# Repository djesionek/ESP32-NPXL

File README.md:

# ESP_NPXL breakout board
This is a breakout board for the ESP-32S (ESP32 chip) and a continuation of the [ESP-NPXL Project](https://github.com/djesionek/ESP-NPXL)

*Work is still in progress*

# Features
Some features that are planned to be added over the old ESP-NPXL project are:

- Integrated FTDI chip and micro USB or USB Type-C connector for easier development
- Integrated LiPo management enabling the chip to charge the battery while connected and seamlessly use its charge after disconnected
- Smaller footprint

# Contributing
Feel free contributing or doing whatever with this design. As board design is only a hobby of mine it's probably 
not a good design anyway ;)

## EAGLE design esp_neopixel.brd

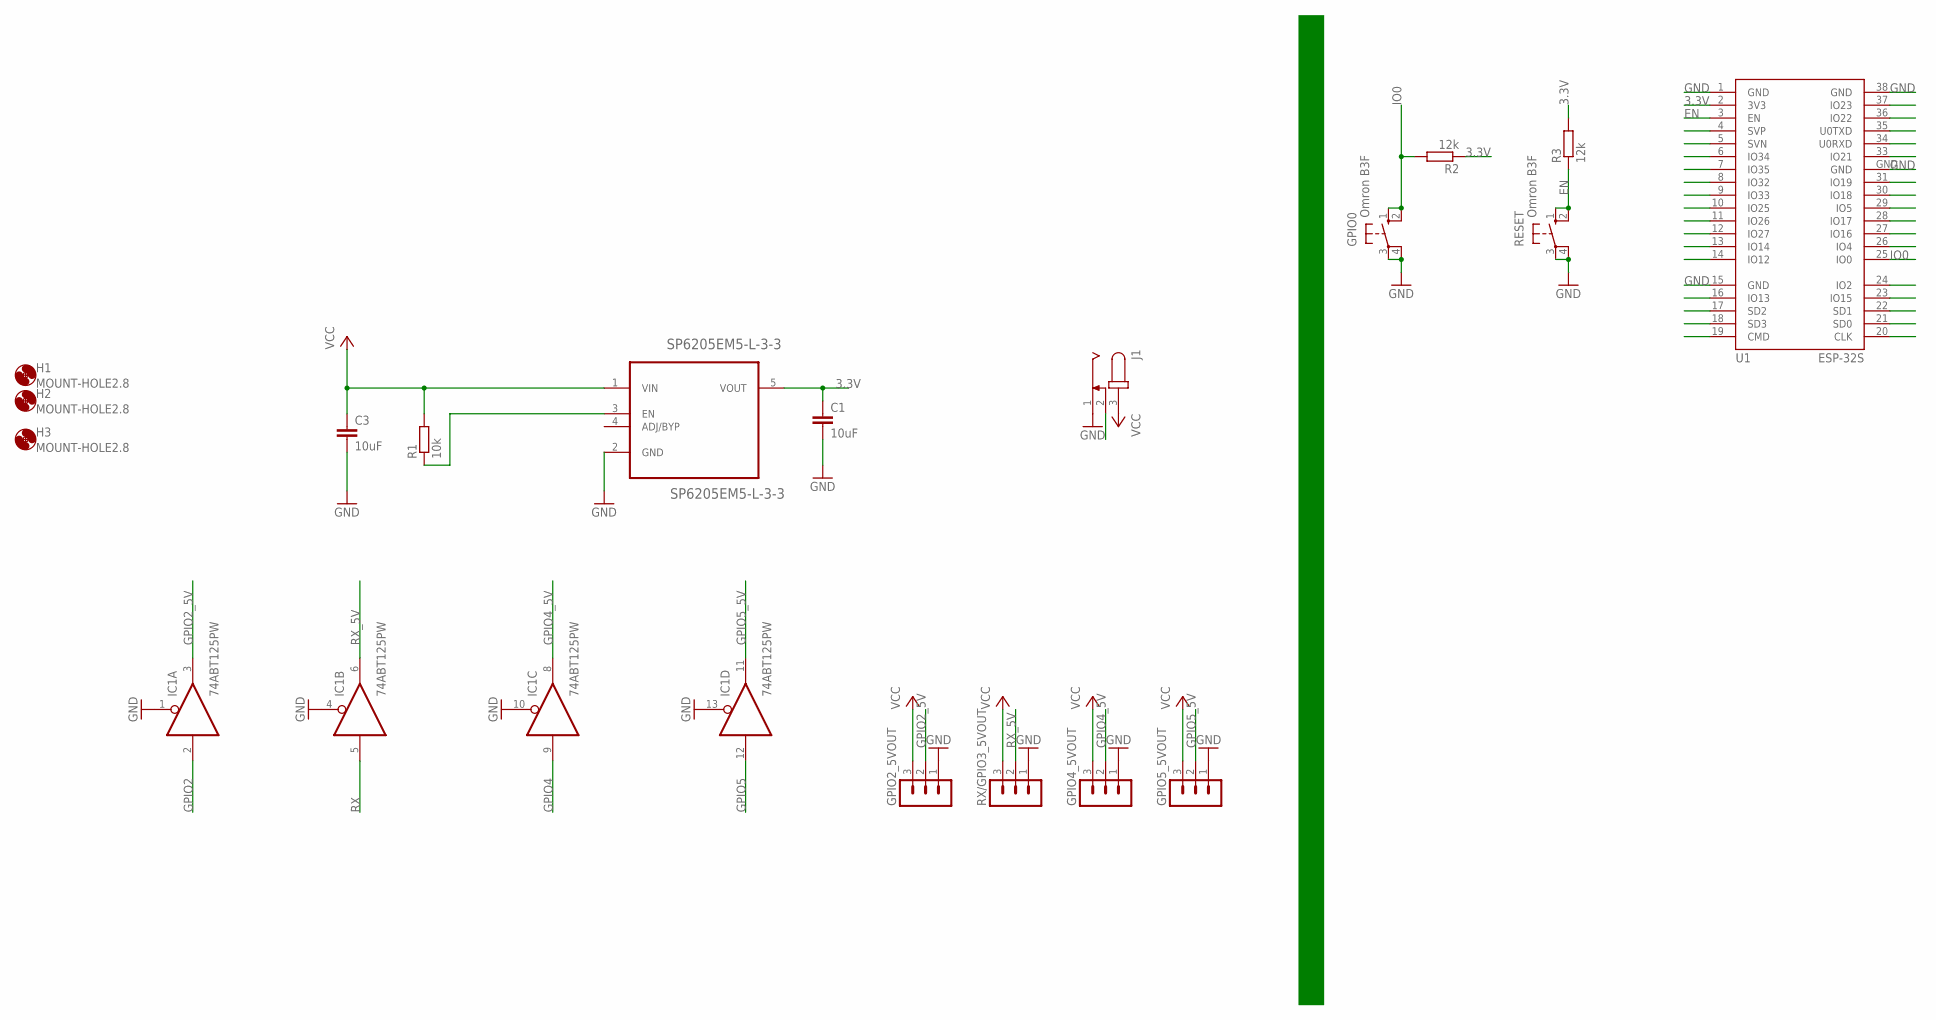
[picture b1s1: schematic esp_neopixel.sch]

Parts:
C1, C3: 10uF; C0805K
GPIO0: Omron B3F; B3F-10XX
GPIO2_5VOUT, GPIO4_5VOUT, GPIO5_5VOUT: MA03-1
H1, H2, H3: MOUNT-HOLE2.8; 2,8
IC1: 74ABT125PW; TSSOP14
J1: JACK-PLUG1; SPC4078
R1: 10k; M0805
R2, R3: 12k; M0805
RESET: Omron B3F; B3F-10XX
RX/GPIO3_5VOUT: MA03-1
SP6205EM5-L-3-3: SP6205EM5-L-3-3; SOT95P280X145-5N
U1: ESP-32S

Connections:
3.3V: C1.1, R2.1, R3.2, SP6205EM5-L-3-3.5 (VOUT), U1.2 (3V3)
EN: R3.1, RESET.1 (S), RESET.2 (S1), U1.3 (EN)
GND: C1.2, C3.2, GPIO0.3, GPIO0.4 (P1), GPIO2_5VOUT.1, GPIO4_5VOUT.1, GPIO5_5VOUT.1, IC1.1 (OE), IC1.4 (OE), IC1.7 (GND), IC1.10 (OE), IC1.13 (OE), J1.1, RESET.3, RESET.4 (P1), RX/GPIO3_5VOUT.1, SP6205EM5-L-3-3.2 (GND), U1.1 (GND), U1.15 (GND), U1.38 (GND), U1.GND
GPIO2: IC1.2 (I)
GPIO2_5V: GPIO2_5VOUT.2, IC1.3 (O)
GPIO4: IC1.9 (I)
GPIO4_5V: GPIO4_5VOUT.2, IC1.8 (O)
GPIO5: IC1.12 (I)
GPIO5_5V: GPIO5_5VOUT.2, IC1.11 (O)
IO0: GPIO0.1 (S), GPIO0.2 (S1), R2.2, U1.25 (IO0)
unnamed: R1.1, SP6205EM5-L-3-3.3 (EN)
RX: IC1.5 (I)
RX_5V: IC1.6 (O), RX/GPIO3_5VOUT.2
VCC: C3.1, GPIO2_5VOUT.3, GPIO4_5VOUT.3, GPIO5_5VOUT.3, IC1.14 (VCC), J1.3, R1.2, RX/GPIO3_5VOUT.3, SP6205EM5-L-3-3.1 (VIN)

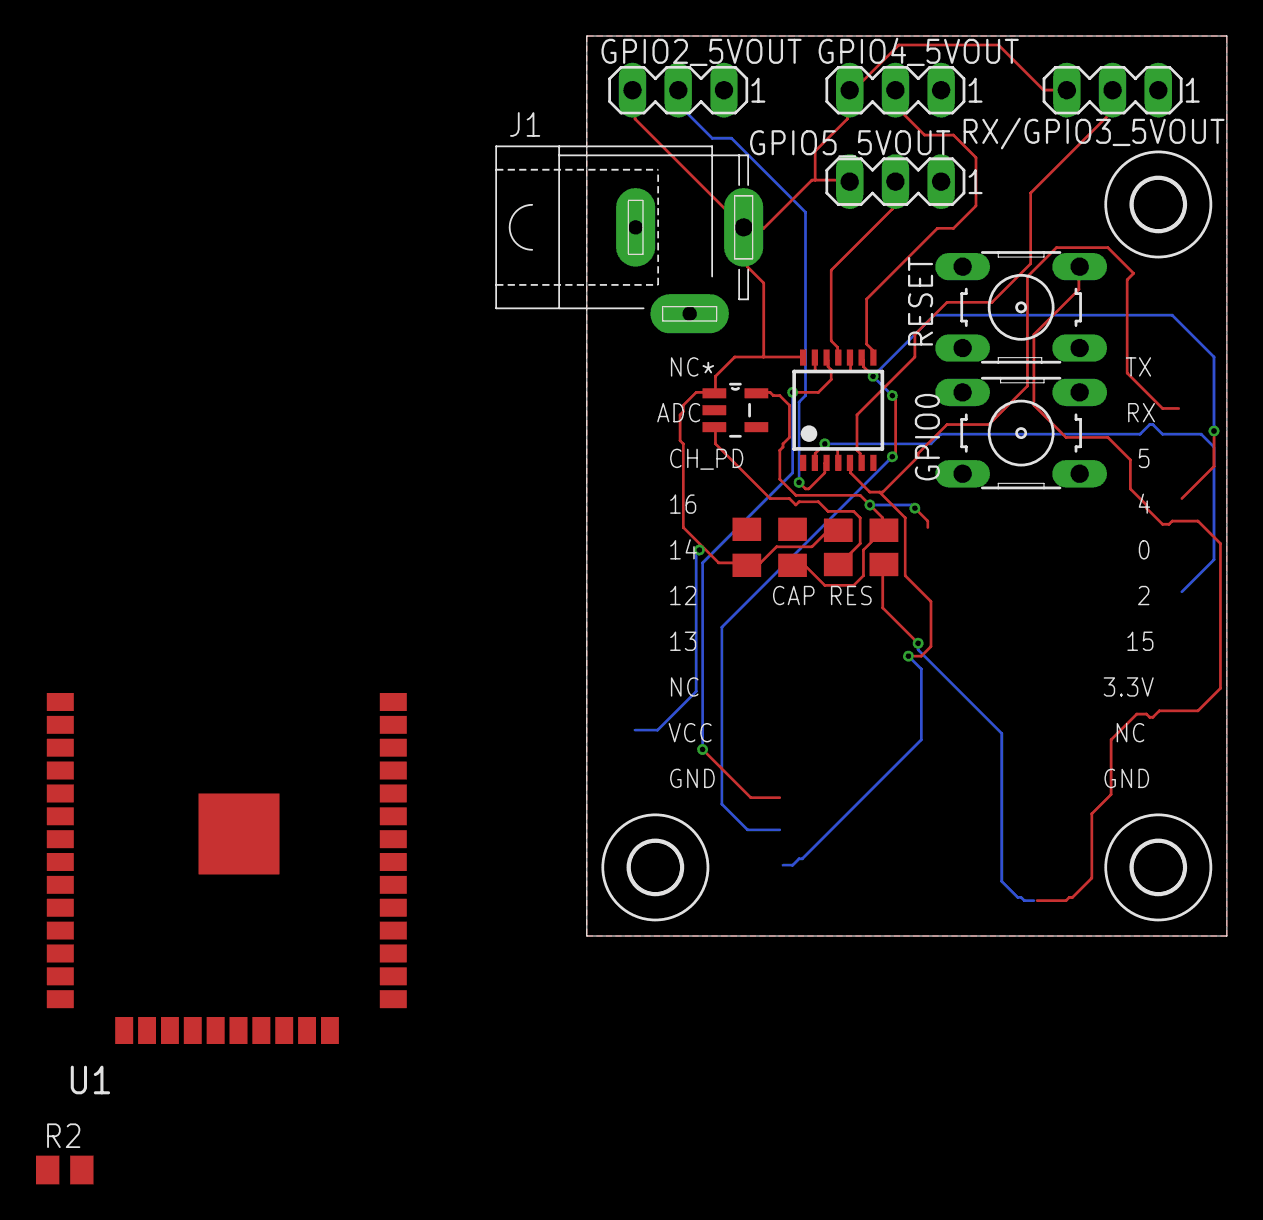
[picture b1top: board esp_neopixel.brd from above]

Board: 2 copper layers, 35.6 x 50.0 mm, 18 parts (0 on the bottom side), 10 nets.

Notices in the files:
parts and their libraries:
esp32: Creative Commons Attribution-ShareAlike 4.0 International
